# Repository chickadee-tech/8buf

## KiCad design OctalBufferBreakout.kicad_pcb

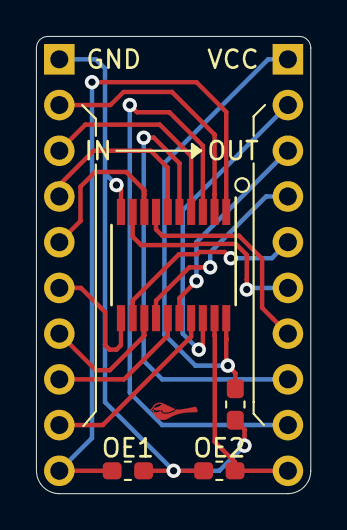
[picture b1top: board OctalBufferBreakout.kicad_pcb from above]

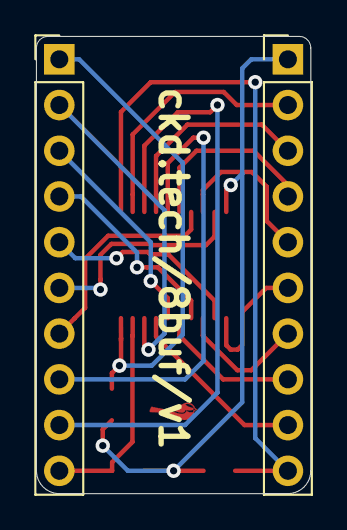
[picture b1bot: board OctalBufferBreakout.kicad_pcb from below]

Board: 2 copper layers, 15.2 x 25.4 mm, 6 parts (2 on the bottom side), 20 nets.

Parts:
C1: C_Small; C_0603_1608Metric_Pad1.05x0.95mm_HandSolder
J1, J2: Conn_01x10_Male; PinHeader_1x10_P2.54mm_Vertical
R1, R2: 10k; R_0603_1608Metric_Pad1.05x0.95mm_HandSolder
U1: 74LS244; TSSOP-20_4.4x6.5mm_P0.65mm

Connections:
/1~OE: J1.10, R1.1, U1.1
/2~OE: J2.10, R2.1, U1.19
GND: C1.2, J1.1, R1.2, R2.2, U1.10
unnamed: J1.2, U1.2
unnamed: J1.3, U1.4
unnamed: J1.4, U1.6
unnamed: J1.5, U1.8
unnamed: J1.6, U1.11
unnamed: J1.7, U1.13
unnamed: J1.8, U1.15
unnamed: J1.9, U1.17
unnamed: J2.2, U1.18
unnamed: J2.3, U1.16
unnamed: J2.4, U1.14
unnamed: J2.5, U1.12
unnamed: J2.6, U1.9
unnamed: J2.7, U1.7
unnamed: J2.8, U1.5
unnamed: J2.9, U1.3
VCC: C1.1, J2.1, U1.20
